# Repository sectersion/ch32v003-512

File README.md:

# STASIS — 512-Core CH32V003 RISC-V Compute Cluster

> A massively parallel, modular RISC-V compute cluster built from 512 CH32V003 microcontrollers, designed for neural network inference, extremely slow graphics rendering, and embarrassingly parallel workloads.

---

## Overview

CH32V003512 is a custom compute cluster built entirely from WCH CH32V003 RISC-V microcontrollers. 512 worker cores are organized across 32 hot-swappable modules, connected via a hierarchical SPI fabric to a host MCU that interfaces with a PC over USB. The system is designed for parallel workloads including neural network inference, raytracing, cellular automata, and any embarrassingly parallel computation.

I created this project inspired by [bitluni's lab](https://bitluni.net/) take on a ch32v003 cluster. The architecture was inspired by my prior knowledge of chip design. My goal is to emulate tiny distributed computing in an easy to understand way.

This project was built for [Hack Club Stasis](https://stasis.hackclub.com).

---

## Architecture

```
PC (USB/Serial)
└── Host MCU — CH32V307 (USB-HS)
    └── SPI Bus
        ├── Column Controller 0 — CH32V307
        │   ├── PSU (5V → 3.3V, ~5A)
        │   └── Slot Router ×8 — CH32V203
        │       └── 16× CH32V003 Worker Cores (via SPI ring)
        ├── Column Controller 1 — CH32V307
        ├── Column Controller 2 — CH32V307
        └── Column Controller 3 — CH32V307
```

### MCU Roles

| Role | MCU | Count | Notes |
|---|---|---|---|
| Worker Core | CH32V003J4M6 (QFN-20) | 512 | 3×3mm, 48MHz, 2KB RAM |
| Slot Router | CH32V203C8T6 (QFN-48) | 32 | Dual SPI + DMA, manages 16 workers |
| Column Controller | CH32V307VCT6 | 4 | FPU, manages 8 slot routers + PSU |
| Host MCU | CH32V307VCT6 | 1 | USB-HS to PC, top-level scheduler |
| **Total** | | **549** | |

---

## Hardware

### System Boards

| Board | Qty | Description |
|---|---|---|
| **Module Board** | 32 | 16× CH32V003 workers, M.2 Key B edge connector, 20 LEDs |
| **Backplane** | 1 | 4 removable columns using M.2 Key B, host MCU, system status LEDs, ATX power input |
| **Column Board** | 4 | 8× M.2 slots, CH32V307 column controller, CH32V203 slot routers, PSU |
| **Programmer Board** | 1 | Programs one module at a time via SWD, separate project |

NOTE: May need 2 seperate programmer boards for columns and compute modules, because they don't follow the same pin layout.

### Module Board

- **Size**: M.2 2260 (22×60mm), 4-layer PCB
- **Workers**: 16× CH32V003J4M6 in QFN-20 (3×3mm each)
- **Interface**: M.2 Key B, 0.5mm pin pitch
- **LEDs**: 16× green per-worker activity + 4× status (power, SPI, reset, ready)
- **Topology**: SPI daisy-chain ring, slot router as master

### Backplane

- **Columns**: 4× removable column boards via M.2 Key A/E connector
- **Power**: ATX PSU input, per-column regulation
- **Host MCU**: CH32V307 with USB-HS
- **LEDs**: Per-slot status (128), per-column status (20), system status bank (20)
- **Hot-swap**: Per-slot AP2141 load switch, soft-eject protocol

### M.2 Module Pinout (Key B, 75 pins)

| Signal | Pins | Notes |
|---|---|---|
| GND | 11 | Distributed |
| 3.3V | 9 | ~4.5A capacity |
| SPI (CLK, MOSI, MISO, CS) | 4 | Slot router ↔ module ring master |
| NRST_ALL | 1 | Global worker reset |
| STATUS | 1 | Module insertion detect |
| SLOT_ID[0:4] | 5 | 5-bit address strapping (32 slots) |
| PWR_EN | 1 | Hot-swap load switch enable |
| PWR_GOOD | 1 | Power good feedback |
| RESERVED | 2 | Future expansion |

> SWD is handled entirely on the backplane by the CH32V203 slot router.  
> No SWD signals cross the M.2 connector during normal operation.

---

## LED Map

| Location | Count | Colors | Purpose |
|---|---|---|---|
| Per worker (×512) | 512 | Green | Computation activity |
| Per module status (×32) | 128 | R/B/Y/W | Power, SPI, reset, ready |
| Backplane per-slot (×32) | 128 | G/B/R/Y | Slot power, traffic, fault, programming |
| Backplane per-column (×4) | 20 | G/R/B/Y/W | PSU, controller, busy, idle |
| Backplane system status | 20 | Various | USB, SPI bus, power rails, fault |
| Programmer board | 21 | Various | Programming status per worker |
| **Total** | **829** | | |

---

## Software / SDK

A custom SDK is being developed targeting all tiers of the hierarchy:
It will be a combination of a custom compiler, communications package and flasher, and will have a 80-120 instruction set for programming the workers. The compiler will generate the code into arduino .INO files, the flasher will autonomously flash the worker and column modules. The communications package is in charge of talking to the main MCU using Serial via USB. It is a very heavy SDK for a very heavy board. The board will probably weight like 5 pounds.

### Workload Model

Jobs are tiled into small packets (<512 bytes) to fit within router SRAM constraints. The host PC dispatches job tiles down the hierarchy:

```
PC -> Host MCU -> Column Controller -> Slot Router -> Worker Core
                                                  |
PC <- Host MCU <- Column Controller <- Slot Router <- Result
```

---

## BOM Summary

| Category | Approx. Cost |
|---|---|
| Worker MCUs (512× CH32V003) | ~$61 |
| Slot routers (32× CH32V203) | ~$16 |
| Column controllers + host (5× CH32V307) | ~$12.50 |
| PCBs (JLC, 4-layer) | TBD |
| PCBA assembly | TBD |
| M.2 connectors (×32 module + ×4 column) | TBD |
| Passives, LEDs, power components | TBD |
| 5-port USB-C power brick | ~$30 |
| **Estimated Total** | **$500–1500** |

---

## Project Status

- [x] System architecture defined
- [x] MCU selection finalized
- [x] M.2 pinout spec complete
- [x] LED strategy defined
- [x] KiCad schematic — top level hierarchy
- [x] KiCad schematic — module board
- [ x KiCad schematic — backplane
- [WIP] KiCad schematic — column board
- [ ] KiCad schematic — programmer board
- [ ] PCB layout — module board
- [ ] PCB layout — backplane
- [ ] PCB layout — column board
- [ ] Bring-up and testing
- [ ] SDK — worker firmware
- [ ] SDK — router/controller firmware
- [ ] SDK — PC interface
- [ ] Compute kernels

---

## Tools & Fabrication

- **EDA**: KiCad 9
- **PCB Fab**: JLCPCB (4-layer and 2-layer, PCBA)
- **Programming**: Custom programmer board (separate project)
- **Languages**: C (firmware), Python / C++ / Rust (host SDK)

---

## Inspiration

Heavily inspired by bitluni's CH32V003 cluster. STASIS scales the concept to 512 cores with a structured hierarchical fabric, hot-swap modules, custom tooling, and a full SDK.

---

## License

MIT License — see [LICENSE](LICENSE) for details.

---

## Author

Built for Hack Club Stasis.  
If you're reading this and you've also built something unhinged out of cheap RISC-V chips, let's talk.

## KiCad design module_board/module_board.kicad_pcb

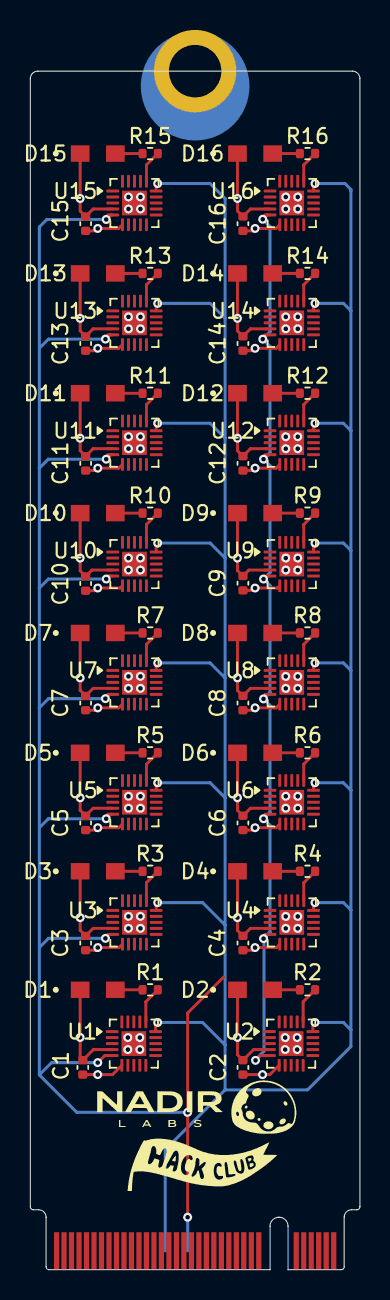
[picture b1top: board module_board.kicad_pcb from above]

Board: 4 copper layers, 22.0 x 80.0 mm, 65 parts (0 on the bottom side), 55 nets.

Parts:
C1, C2, C3, C4, C5, C6, C7, C8, C9, C10, C11, C12, C13, C14, C15, C16: 100nF; C_0402_1005Metric
D1, D2, D3, D4, D5, D6, D7, D8, D9, D10, D11, D12, D13, D14, D15, D16: APT2012SGC (GREEN); APT2012SGC
R1, R2, R3, R4, R5, R6, R7, R8, R9, R10, R11, R12, R13, R14, R15, R16: 220; R_0402_1005Metric
U1, U2, U3, U4, U5, U6, U7, U8, U9, U10, U11, U12, U13, U14, U15, U16: CH32V003FxUx; QFN-20-1EP_3x3mm_P0.4mm_EP1.65x1.65mm
U$2: M.2-B-KEY

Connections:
+3V3: C1.1, C2.1, C3.1, C4.1, C5.1, C6.1, C7.1, C8.1, C9.1, C10.1, C11.1, C12.1, C13.1, C14.1, C15.1, C16.1, U1.6 (VDD), U2.6 (VDD), U3.6 (VDD), U4.6 (VDD), U5.6 (VDD), U6.6 (VDD), U7.6 (VDD), U8.6 (VDD), U9.6 (VDD), U10.6 (VDD), U11.6 (VDD), U12.6 (VDD), U13.6 (VDD), U14.6 (VDD), U15.6 (VDD), U16.6 (VDD)
/module/module_0/MOD_SPI_MISO: U1.2 (PA1), U2.3 (PA2)
/module/module_1/MOD_SPI_MISO: U2.2 (PA1), U3.3 (PA2)
/module/module_2/MOD_SPI_MISO: U3.2 (PA1), U4.3 (PA2)
/module/module_3/MOD_SPI_MISO: U4.2 (PA1), U5.3 (PA2)
/module/module_4/MOD_SPI_MISO: U5.2 (PA1), U6.3 (PA2)
/module/module_5/MOD_SPI_MISO: U6.2 (PA1), U7.3 (PA2)
/module/module_6/MOD_SPI_MISO: U7.2 (PA1), U8.3 (PA2)
/module/module_7/MOD_SPI_MISO: U8.2 (PA1), U9.3 (PA2)
/module/module_8/MOD_SPI_MISO: U9.2 (PA1), U10.3 (PA2)
/module/module_10/MOD_SPI_MISO: U11.2 (PA1), U12.3 (PA2)
/module/module_10/MOD_SPI_MOSI: U10.2 (PA1), U11.3 (PA2)
/module/module_11/MOD_SPI_MISO: U12.2 (PA1), U13.3 (PA2)
/module/module_12/MOD_SPI_MISO: U13.2 (PA1), U14.3 (PA2)
/module/module_13/MOD_SPI_MISO: U14.2 (PA1), U15.3 (PA2)
/module/module_14/MOD_SPI_MISO: U15.2 (PA1), U16.3 (PA2)
GND: C1.2, C2.2, C3.2, C4.2, C5.2, C6.2, C7.2, C8.2, C9.2, C10.2, C11.2, C12.2, C13.2, C14.2, C15.2, C16.2, D1.1, D2.1, D3.1, D4.1, D5.1, D6.1, D7.1, D8.1, D9.1, D10.1, D11.1, D12.1, D13.1, D14.1, D15.1, D16.1, U1.4 (VSS), U1.21 (VSS), U2.4 (VSS), U2.21 (VSS), U3.4 (VSS), U3.21 (VSS), U4.4 (VSS), U4.21 (VSS), U5.4 (VSS), U5.21 (VSS), U6.4 (VSS), U6.21 (VSS), U7.4 (VSS), U7.21 (VSS), U8.4 (VSS), U8.21 (VSS), U9.4 (VSS), U9.21 (VSS), U10.4 (VSS), U10.21, U11.4 (VSS), U11.21 (VSS), U12.4 (VSS), U12.21 (VSS), U13.4 (VSS), U13.21 (VSS), U14.4 (VSS), U14.21 (VSS), U15.4 (VSS), U15.21 (VSS), U16.4 (VSS), U16.21 (VSS)
MOD_CS: U1.15 (PD1), U2.15 (PD1), U3.15 (PD1), U4.15 (PD1), U5.15 (PD1), U6.15 (PD1), U7.15 (PD1), U8.15 (PD1), U9.15 (PD1), U10.15 (PD1), U11.15 (PD1), U12.15 (PD1), U13.15 (PD1), U14.15 (PD1), U15.15 (PD1), U16.15 (PD1), U$2.P$46
MOD_SPI_CLK: U1.5 (PD0), U2.5 (PD0), U3.5 (PD0), U4.5 (PD0), U5.5 (PD0), U6.5 (PD0), U7.5 (PD0), U8.5 (PD0), U9.5 (PD0), U10.5 (PD0), U11.5 (PD0), U12.5 (PD0), U13.5 (PD0), U14.5 (PD0), U15.5 (PD0), U16.5 (PD0), U$2.P$40
MOD_STATUS: U1.1 (PD7), U2.1 (PD7), U3.1 (PD7), U4.1 (PD7), U5.1 (PD7), U6.1 (PD7), U7.1 (PD7), U8.1 (PD7), U9.1 (PD7), U10.1 (PD7), U11.1 (PD7), U12.1 (PD7), U13.1 (PD7), U14.1 (PD7), U15.1 (PD7), U16.1 (PD7)
unnamed: D1.2, R1.1
unnamed: D2.2, R2.1
unnamed: D3.2, R3.1
unnamed: D4.2, R4.1
unnamed: D5.2, R5.1
unnamed: D6.2, R6.1
unnamed: D7.2, R7.1
unnamed: D8.2, R8.1
unnamed: D9.2, R9.1
unnamed: D10.2, R10.1
unnamed: D11.2, R11.1
unnamed: D12.2, R12.1
unnamed: D13.2, R13.1
unnamed: D14.2, R14.1
unnamed: D15.2, R15.1
unnamed: D16.2, R16.1
unnamed: R1.2, U1.16 (PD2)
unnamed: R2.2, U2.16 (PD2)
unnamed: R3.2, U3.16 (PD2)
unnamed: R4.2, U4.16 (PD2)
unnamed: R5.2, U5.16 (PD2)
unnamed: R6.2, U6.16 (PD2)
unnamed: R7.2, U7.16 (PD2)
unnamed: R8.2, U8.16 (PD2)
unnamed: R9.2, U9.16 (PD2)
unnamed: R10.2, U10.16 (PD2)
unnamed: R11.2, U11.16 (PD2)
unnamed: R12.2, U12.16 (PD2)
unnamed: R13.2, U13.16 (PD2)
unnamed: R14.2, U14.16 (PD2)
unnamed: R15.2, U15.16 (PD2)
unnamed: R16.2, U16.16 (PD2)
SWDCLK: U1.19 (PD5), U2.19 (PD5), U3.19 (PD5), U4.19 (PD5), U5.19 (PD5), U6.19 (PD5), U7.19 (PD5), U8.19 (PD5), U9.19 (PD5), U10.19 (PD5), U11.19 (PD5), U12.19 (PD5), U13.19 (PD5), U14.19 (PD5), U15.19 (PD5), U16.19 (PD5), U$2.P$9
SWDIO: U1.20 (PD6), U2.20 (PD6), U3.20 (PD6), U4.20 (PD6), U5.20 (PD6), U6.20 (PD6), U7.20 (PD6), U8.20 (PD6), U9.20 (PD6), U10.20 (PD6), U11.20 (PD6), U12.20 (PD6), U13.20 (PD6), U14.20 (PD6), U15.20 (PD6), U16.20 (PD6), U$2.P$7
SYS_NRST: U1.17 (PD3), U2.17 (PD3), U3.17 (PD3), U4.17 (PD3), U5.17 (PD3), U6.17 (PD3), U7.17 (PD3), U8.17 (PD3), U9.17 (PD3), U10.17 (PD3), U11.17 (PD3), U12.17 (PD3), U13.17 (PD3), U14.17 (PD3), U15.17 (PD3), U16.17 (PD3)

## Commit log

2026-03-13 Revise README with project details and specifications
    Updated project name and added detailed project overview, architecture, hardware specifications, software SDK information, and project status.
2026-03-14 upload 1
2026-03-14 upload 2
2026-03-14 upload 3
2026-03-14 Add M.2 Main Receptacle Datasheet
    This document provides detailed specifications and operational guidelines for the M.2 Key A/E receptacle used in the STASIS 512-core CH32V003 Compute Cluster, including electrical characteristics, pi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
2026-03-14 upload 4
2026-03-15 feat: create module connector system
2026-03-16 Revise README for clarity and additional details
    Updated project description and details in README.
2026-03-16 feat: start module board with daisy-chain SPI interface
2026-03-16 Rename project to CH32V003512 in README
    Updated project name from 'STASIS' to 'CH32V003512' in the overview section.
2026-03-18 feat: finish all essential schematics (i think?)
2026-03-19 ruined all the traces on MB
